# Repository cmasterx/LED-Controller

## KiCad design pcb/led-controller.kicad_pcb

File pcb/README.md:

# LED Controller PCB
PCB schematic and layout for MiOrigin Controller designed on KiCAD

## TODO
- [x] Configure .gitignore for PCB project
- [x] Add KiCAD ATL Project as library dependency to the LED Controller project
  -  ATL Library added as git submodule, but project currently has no dependency to the ATL library

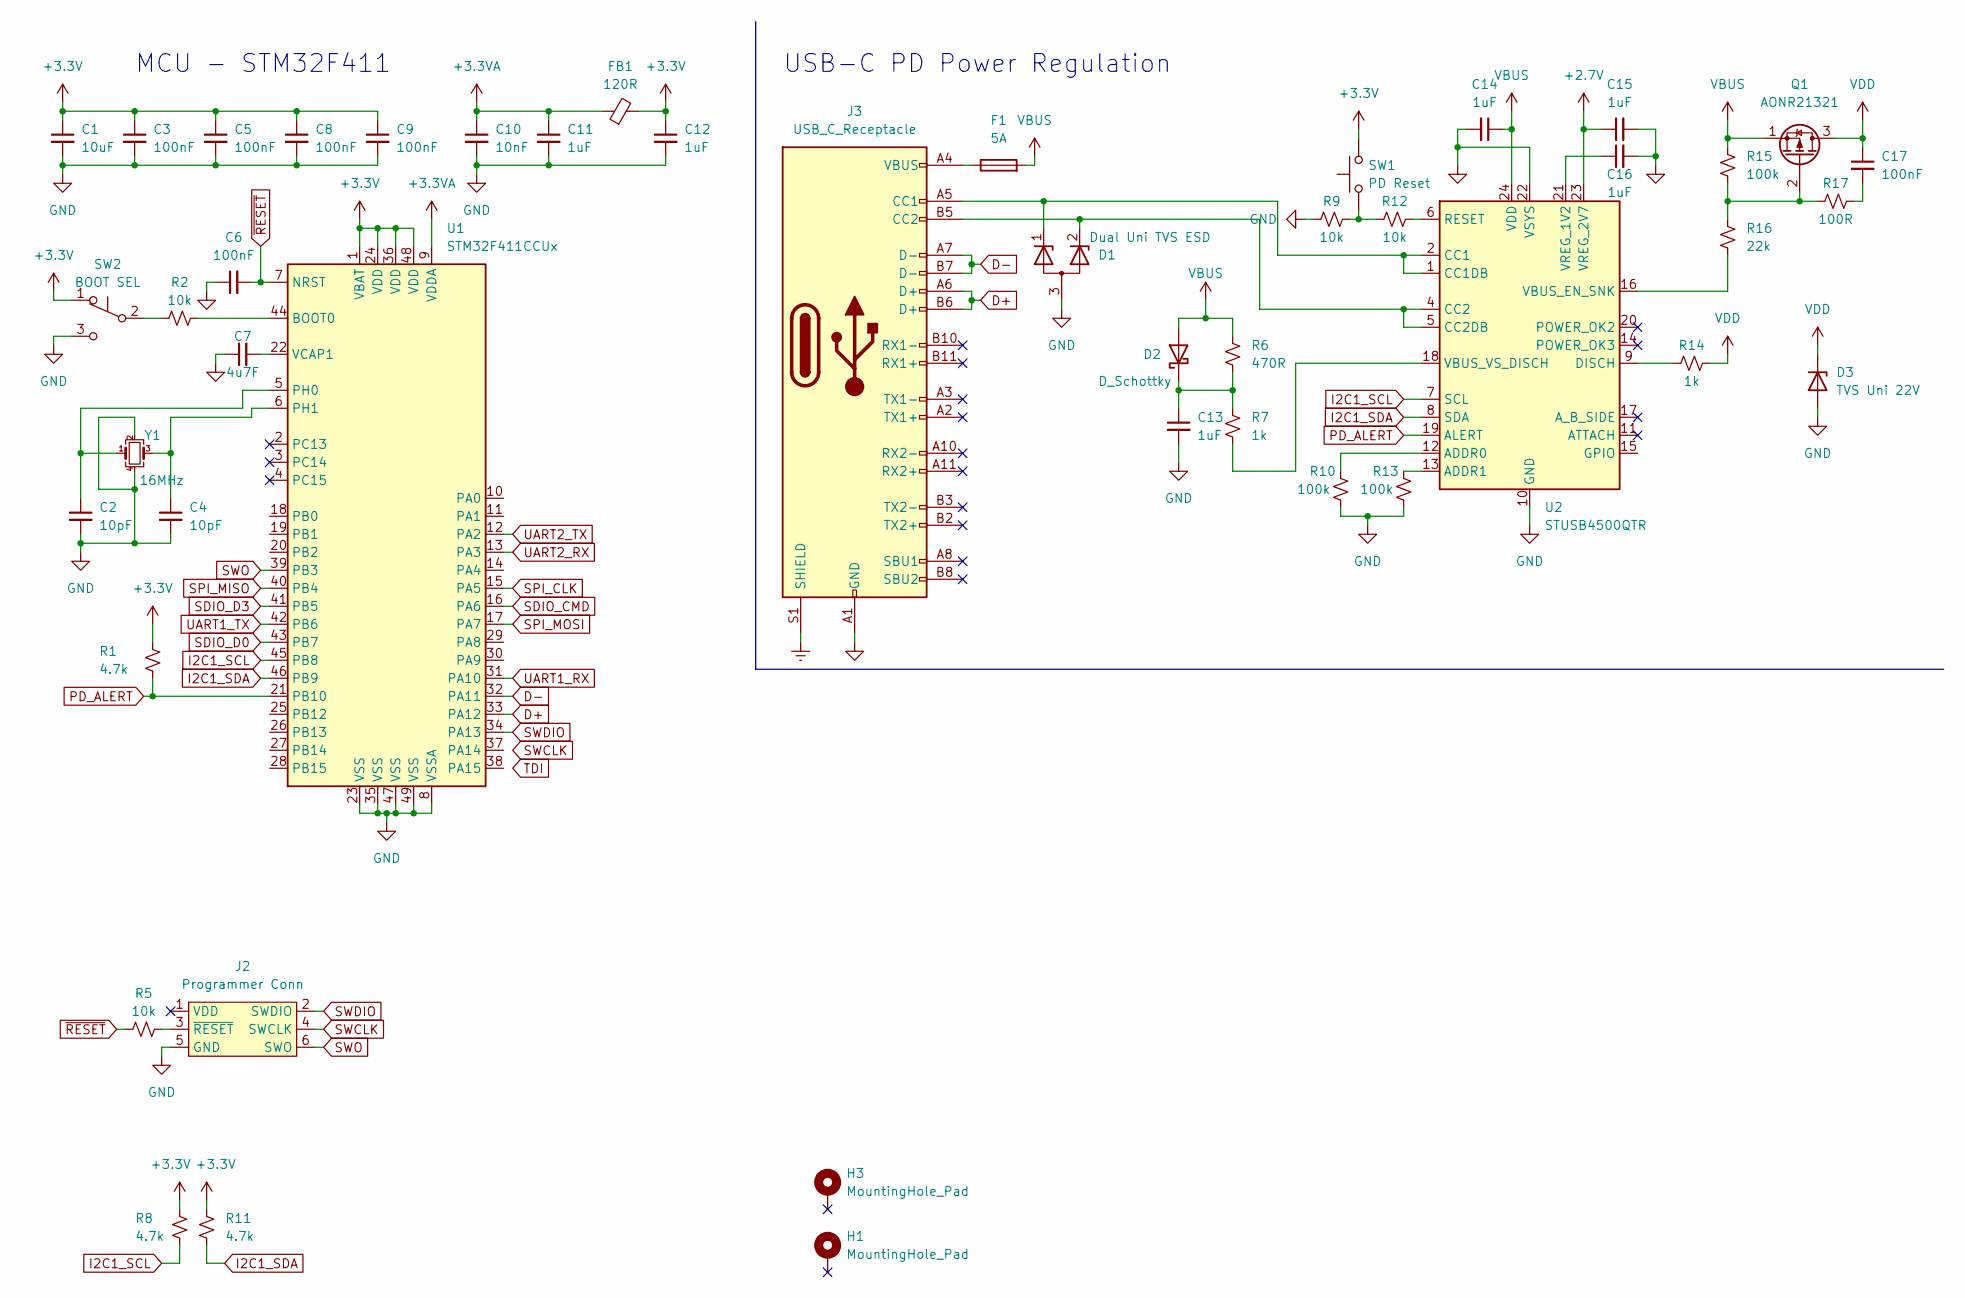
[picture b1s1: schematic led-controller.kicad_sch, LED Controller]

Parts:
C1: 10uF; C_0603_1608Metric
C2, C4: 10pF; C_0603_1608Metric
C3, C5, C6, C8, C9, C17: 100nF; C_0603_1608Metric
C7: 4u7F; C_0603_1608Metric
C10: 10nF; C_0603_1608Metric
C11, C12, C13, C14, C15, C16: 1uF; C_0603_1608Metric
D1: Dual Uni TVS ESD
D2: D_Schottky
D3: TVS Uni 22V
F1: 5A; Littlefuse-154
FB1: 120R
H1, H3: MountingHole_Pad; MountingHole_2.2mm_M2_Pad
J2: Programmer Conn; Tag-Connect_TC2030-IDC-FP_2x03_P1.27mm_Vertical
J3: USB_C_Receptacle; USB_C_Receptacle_Amphenol_12401548E4-2A
Q1: AONR21321
R1, R8, R11: 4.7k; R_0603_1608Metric
R2, R5, R9, R12: 10k; R_0603_1608Metric
R6: 470R; R_0603_1608Metric
R7, R14: 1k; R_0603_1608Metric
R10, R13, R15: 100k; R_0603_1608Metric
R16: 22k; R_0603_1608Metric
R17: 100R; R_0603_1608Metric
SW1: PD Reset; SW_SPST_B3U-1000P
SW2: BOOT SEL; SW_DIP_SPSTx01_Slide_Copal_CVS-01xB_W5.9mm_P1mm
U1: STM32F411CCUx; QFN-48-1EP_7x7mm_P0.5mm_EP5.6x5.6mm
U2: STUSB4500QTR; QFN-24-1EP_4x4mm_P0.5mm_EP2.7x2.7mm
Y1: 16MHz; Crystal_SMD_Abracon_ABM8G-4Pin_3.2x2.5mm

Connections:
+2V7: C15.1, U2.23 (VREG_2V7)
+3.3V: C1.1, C3.1, C5.1, C8.1, C9.1, C12.1, FB1.2, R1.1, R8.1, R11.1, SW1.2, SW2.1 (A), U1.1 (VBAT), U1.24 (VDD), U1.36 (VDD), U1.48 (VDD)
+3.3VA: C10.1, C11.1, FB1.1, U1.9 (VDDA)
D+: J3.A6 (D+), J3.B6 (D+), U1.33 (PA12)
D-: J3.A7 (D-), J3.B7 (D-), U1.32 (PA11)
Earth: J3.S1 (SHIELD)
GND: C1.2, C2.2, C3.2, C4.2, C5.2, C6.1, C7.1, C8.2, C9.2, C10.2, C11.2, C12.2, C13.2, C14.2, C15.2, C16.2, D1.3 (A), D3.2 (A), J2.5 (GND), J3.A1 (GND), J3.A12 (GND), J3.B1 (GND), J3.B12 (GND), R9.1, R10.1, R13.1, SW2.3 (C), U1.8 (VSSA), U1.23 (VSS), U1.35 (VSS), U1.47 (VSS), U1.49 (VSS), U2.10 (GND), U2.22 (VSYS), U2.25 (GND), Y1.2, Y1.4
I2C1_SCL: R8.2, U1.45 (PB8), U2.7 (SCL)
I2C1_SDA: R11.2, U1.46 (PB9), U2.8 (SDA)
unnamed: C2.1, U1.5 (PH0), Y1.1
unnamed: C4.1, U1.6 (PH1), Y1.3
unnamed: C7.2, U1.22 (VCAP1)
unnamed: C13.1, D2.1 (K), R6.2, R7.1
unnamed: C17.2, R17.2
unnamed: D1.1 (K), J3.A5 (CC1), U2.1 (CC1DB), U2.2 (CC1)
unnamed: D1.2 (K), J3.B5 (CC2), U2.4 (CC2), U2.5 (CC2DB)
unnamed: F1.1, J3.A4 (VBUS), J3.A9 (VBUS), J3.B4 (VBUS), J3.B9 (VBUS)
unnamed: J2.3 (~RESET), R5.2
unnamed: Q1.2 (G), R15.2, R16.1, R17.1
unnamed: R2.1, SW2.2 (B)
unnamed: R2.2, U1.44 (BOOT0)
unnamed: R7.2, U2.18 (VBUS_VS_DISCH)
unnamed: R10.2, U2.12 (ADDR0)
unnamed: R9.2, R12.1, SW1.1
unnamed: R12.2, U2.6 (RESET)
unnamed: R13.2, U2.13 (ADDR1)
unnamed: R14.1, U2.9 (DISCH)
unnamed: R16.2, U2.16 (VBUS_EN_SNK)
unnamed: C16.1, U2.21 (VREG_1V2)
PD_ALERT: R1.2, U1.21 (PB10), U2.19 (ALERT)
SDIO_CMD: U1.16 (PA6)
SDIO_D0: U1.43 (PB7)
SDIO_D3: U1.41 (PB5)
SPI_CLK: U1.15 (PA5)
SPI_MISO: U1.40 (PB4)
SPI_MOSI: U1.17 (PA7)
SWCLK: J2.4 (SWCLK)
SWDIO: J2.2 (SWDIO), U1.34 (PA13)
SWO: J2.6 (SWO), U1.39 (PB3)
UART1_RX: U1.31 (PA10)
UART1_TX: U1.42 (PB6)
UART2_RX: U1.13 (PA3)
UART2_TX: U1.12 (PA2)
VBUS: C14.1, D2.2 (A), F1.2, Q1.1 (S), R6.1, R15.1, U2.24 (VDD)
VDD: C17.1, D3.1 (K), Q1.3 (D), R14.2
~RESET: C6.2, R5.1, U1.7 (NRST)

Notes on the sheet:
MCU - STM32F411
USB-C PD Power Regulation

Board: 4 copper layers, 43 parts (6 on the bottom side), 34 nets, no tracks yet.

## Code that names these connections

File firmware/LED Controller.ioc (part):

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Mcu.Name=STM32F411C(C-E)Ux
Mcu.Package=UFQFPN48
Mcu.UserName=STM32F411CCUx
PA0-WKUP.Signal=S_TIM2_CH1_ETR
PA10.Mode=Asynchronous
PA10.Signal=USART1_RX
PA11.Mode=Device_Only
PA11.Signal=USB_OTG_FS_DM
PA12.Mode=Device_Only
PA12.Signal=USB_OTG_FS_DP
PA13.Mode=JTAG_4_pins
PA13.Signal=SYS_JTMS-SWDIO
PA14.Mode=JTAG_4_pins
PA14.Signal=SYS_JTCK-SWCLK
PA15.Mode=JTAG_4_pins
PA15.Signal=SYS_JTDI
PA2.Mode=Asynchronous
PA2.Signal=USART2_TX
PA3.Mode=Asynchronous
PA3.Signal=USART2_RX
PA5.Mode=Full_Duplex_Master
PA5.Signal=SPI1_SCK
PA6.Mode=SD_4_bits_Wide_bus
PA6.Signal=SDIO_CMD
PA7.Mode=Full_Duplex_Master
PA7.Signal=SPI1_MOSI
PA8.Mode=SD_4_bits_Wide_bus
PA8.Signal=SDIO_D1
PA9.Mode=SD_4_bits_Wide_bus
PA9.Signal=SDIO_D2
PB10.GPIOParameters=GPIO_Label
PB10.GPIO_Label=PD_ALERT
PB10.Signal=GPIO_Input
PB14.GPIOParameters=GPIO_PuPd,GPIO_Label
PB14.GPIO_Label=SDIO_IN
PB14.GPIO_PuPd=GPIO_PULLUP
PB14.Signal=GPIO_Input
PB15.Mode=SD_4_bits_Wide_bus
PB15.Signal=SDIO_CK
PB3.Mode=JTAG_4_pins
PB3.Signal=SYS_JTDO-SWO
PB4.Mode=Full_Duplex_Master
PB4.Signal=SPI1_MISO
PB5.Mode=SD_4_bits_Wide_bus
PB5.Signal=SDIO_D3
PB6.Mode=Asynchronous
PB6.Signal=USART1_TX
PB7.Mode=SD_4_bits_Wide_bus
PB7.Signal=SDIO_D0
PB8.Mode=I2C
PB8.Signal=I2C1_SCL
PB9.Mode=I2C
PB9.Signal=I2C1_SDA
PH0\ -\ OSC_IN.Mode=HSE-External-Oscillator
PH0\ -\ OSC_IN.Signal=RCC_OSC_IN
PH1\ -\ OSC_OUT.Mode=HSE-External-Oscillator
PH1\ -\ OSC_OUT.Signal=RCC_OSC_OUT
RCC.HSE_VALUE=16000000
RCC.SYSCLKFreq_VALUE=96000000
RCC.SYSCLKSource=RCC_SYSCLKSOURCE_PLLCLK
board=custom

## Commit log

2022-12-26 Add initial project firmware
2022-12-26 Add VS Code C and C++ configurations (for Linux)
2022-12-26 WIP Changes
2023-01-01 Experimental tests on Middleware and driver support for LED controller
2023-01-01 Add initial pcb project
2023-01-01 Moved pcb project to correct directory structure, configured pcb project settings, and added git submodule to ATL KiCAD library
2023-01-01 Update pcb .gitignore to ignore cache, backup, and user-specific files
2023-01-01 Update pcb documentation
2023-01-01 Update .gitignore comment
2023-01-02 Link PCB project (schematic and pcb) to ATL KiCAD library
2023-01-11 WIP STUSB4500 (USB-C PD IC)
2023-01-20 M0re pcb progress
2023-01-20 Configured firmware project in parallel with pcb
2023-01-20 Progress on STM32F411 wiring
2023-01-21 Update to lkicad library with required components
2023-01-21 PCB updates
